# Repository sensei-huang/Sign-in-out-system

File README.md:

# Sign-in-out-system
Sign-in-out system code
| Folder | Contains |
| ------ | -------- |
| 3D | 3D files that were printed |
| AppsScripts | Google Apps Scripts code for backend |
| Arduino | Arduino code that was uploaded to the WeMos D1 MiNi |
| Gerber | Gerber files for the PCB board |
| HTML | HTML code for the website |
| Spreadsheet | Google spreadsheet example in xlsx format |

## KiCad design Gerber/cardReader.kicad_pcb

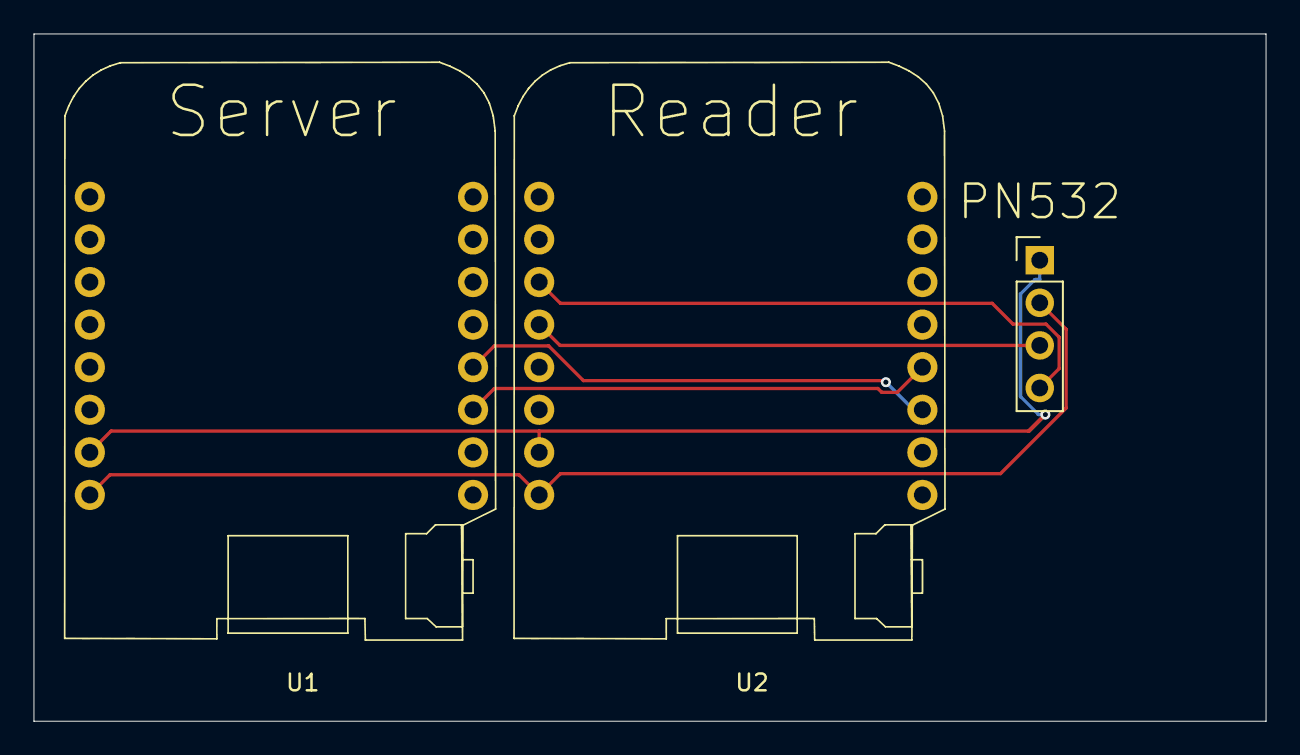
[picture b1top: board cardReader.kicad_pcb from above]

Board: 2 copper layers, 73.5 x 41.0 mm, 3 parts (0 on the bottom side), 6 nets.

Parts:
PN532: Conn_01x04_MountingPin; PinHeader_1x04_P2.54mm_Vertical
U1, U2: WeMos_mini; D1_mini_board

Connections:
unnamed: PN532.1, U1.2 (GND), U2.2 (GND)
unnamed: PN532.2, U1.1 (5V), U2.1 (5V)
unnamed: PN532.3, U2.5 (D2)
unnamed: PN532.4, U2.6 (D1)
unnamed: U1.13 (D6), U2.14 (D7)
unnamed: U1.14 (D7), U2.13 (D6)

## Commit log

2025-08-14 Renamed
2025-09-25 Create Example
